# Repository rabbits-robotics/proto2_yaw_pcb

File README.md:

# proto2_yaw_pcb

## 役割

Yaw 軸の制御基板（Rev B）。Nucleo F303K8 と IMU を載せ、Yaw 軸モータの制御と、砲塔・車体への電源中継を行う。

## 主要部品

| 部品 | 型番 | 用途 |
|---|---|---|
| マイコンボード | NUCLEO-F303K8 | 制御 |
| CAN トランシーバ | MCP2562-E/P | CAN × 2 コネクタ |
| モータドライバ | DRV8835 | Yaw 軸モータ |
| IMU | BNO055 | Yaw 角 |
| 電源入力コネクタ | AMASS XT30U-M × 2 | アクチュエータ系、制御系 |
| 電源出力コネクタ | JST PH 8P × 1、AMASS XT30U-F × 1、JST PH 6P × 2 | アクチュエータ系、制御系 |
| CAN 終端抵抗 | 120 Ω | |

回路図は [proto2_yaw_b.pdf](./proto2_yaw_b.pdf)、部品表は [bom.csv](./bom.csv)、3D は [proto2_yaw_b.step](./proto2_yaw_b.step)。

## ライセンス

© Rabbits Robotics、[CERN-OHL-P-2.0](./LICENSE)。

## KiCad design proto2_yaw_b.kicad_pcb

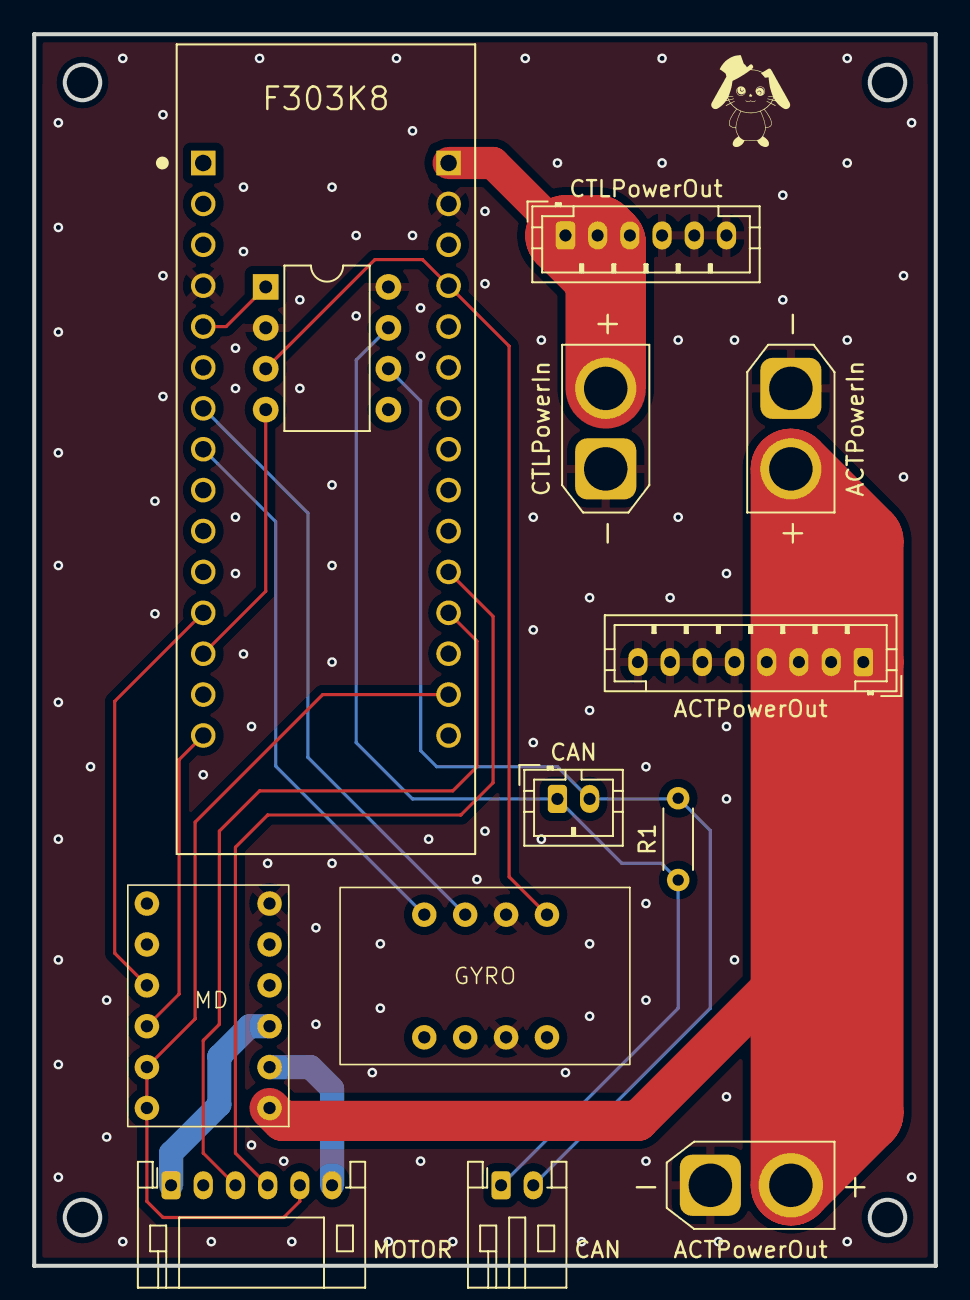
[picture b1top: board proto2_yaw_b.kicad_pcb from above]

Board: 2 copper layers, 56.0 x 76.5 mm, 13 parts (0 on the bottom side), 17 nets.

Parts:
ACTPowerIn: Conn_01x02; AMASS_XT30U-M_1x02_P5.0mm_Vertical
ACTPowerOut: Conn_01x08; JST_PH_B8B-PH-K_1x08_P2.00mm_Vertical
ACTPowerOut#2: Conn_01x02; AMASS_XT30U-F_1x02_P5.0mm_Vertical
CAN: MCP2562-E-P; DIP-8_W7.62mm
CAN#2: Conn_01x02; JST_PH_B2B-PH-K_1x02_P2.00mm_Vertical
CAN#3: Conn_01x02; JST_PH_S2B-PH-K_1x02_P2.00mm_Horizontal
CTLPowerIn: Conn_01x02; AMASS_XT30U-M_1x02_P5.0mm_Vertical
CTLPowerOut: Conn_01x06; JST_PH_B6B-PH-K_1x06_P2.00mm_Vertical
F303K8: NUCLEO-F303K8; MODULE_NUCLEO-F303K8
GYRO: BNO055
MD: DRV8835
MOTOR: Conn_01x06; JST_PH_S6B-PH-K_1x06_P2.00mm_Horizontal
R1: 120; R_Axial_DIN0204_L3.6mm_D1.6mm_P5.08mm_Horizontal

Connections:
+3V3: F303K8.4_14 (+3V3), MD.11 (MODE), MD.12 (VCC), MOTOR.5
+5V: CAN.3 (VDD), F303K8.4_4 (+5V), GYRO.1 (VIN)
+7.5(ACT)V: ACTPowerIn.2, ACTPowerOut.1, ACTPowerOut.2, ACTPowerOut.3, ACTPowerOut.4, ACTPowerOut#2.2, MD.1 (VM)
+7.5(CTL)V: CTLPowerIn.2, CTLPowerOut.1, CTLPowerOut.2, CTLPowerOut.3, F303K8.4_1 (VIN)
/CAN_RX: CAN.4 (RXD), F303K8.3_13 (PA11)
/CAN_TX: CAN.1 (TXD), F303K8.3_5 (PA12)
/ENCODER_A: F303K8.4_12 (PA0), MOTOR.3
/ENCODER_B: F303K8.4_11 (PA1), MOTOR.4
/I2C_SCL: F303K8.3_8 (PB6), GYRO.4 (SCL/R)
/I2C_SDA: F303K8.3_7 (PB7), GYRO.3 (SDA/T)
/MOTOR_ENABLE: F303K8.3_12 (PA8), MD.9 (AIN2/AENBL)
/MOTOR_PHASE: F303K8.3_15 (PB4), MD.10 (AIN/APHASE)
GND: ACTPowerIn.1, ACTPowerOut.5, ACTPowerOut.6, ACTPowerOut.7, ACTPowerOut.8, ACTPowerOut#2.1, CAN.2 (VSS), CAN.8 (STBY), CTLPowerIn.1, CTLPowerOut.4, CTLPowerOut.5, CTLPowerOut.6, F303K8.3_4 (GND_1), F303K8.4_2 (GND_2), GYRO.2 (GND), GYRO.7 (GND), MD.6 (GND), MOTOR.2
unnamed: CAN.7 (CANH), CAN#2.1, CAN#3.1, R1.1
unnamed: CAN.6 (CANL), CAN#2.2, CAN#3.2, R1.2
unnamed: MD.3 (AOUT2), MOTOR.1
unnamed: MD.2 (AOUT1), MOTOR.6
